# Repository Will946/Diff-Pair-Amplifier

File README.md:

# Differential Pair Amplifier for Force Sensing Applications

---

## Overview

A fully differential JFET-based amplifier designed to condition small analog signals from pressure transducers. The amplifier takes in a weak differential signal and amplifies it for readback by a microcontroller. The design is compact enough to mount close to the sensor, minimizing noise pickup before amplification.

Typical use cases for this amplifier topology include:
- Pressure and force transducer signal conditioning
- Strain gauge bridge amplification
- Low-level differential sensor readout in embedded systems
- Any application requiring rejection of common-mode noise on a differential signal line

---

## Circuit Architecture

The amplifier is a **common-source differential pair** using two JFE150DCKR N-channel JFETs with resistive drain loads, biased by a JFET current mirror tail current source.

- **Topology:** Common-source differential pair with resistive load
- **Devices:** 2x JFE150DCKR (signal pair) + 2x JFE150DCKR (current mirror)
- **Drain resistors:** Rp1 = Rn1 = 330 Ohm
- **Tail current:** 24 mA
- **Bias point:** V_GS = 188 mV, I_D = 12.1 mA per branch
- **Supply voltage:** V_DD = 8 V
- **Load capacitance:** 1 pF

---

## DC Operating Point

| Parameter | Value |
|---|---|
| Supply voltage (V_DD) | 8 V |
| Drain voltage (Voutp / Voutn) | 4.02 V |
| Drain current per branch | 12.1 mA |
| Tail current | 24.1 mA |
| Gate bias voltage | 188 mV |
| Total DC current | ~48 mA |
| Total DC power | ~0.38 W |

The drain voltage sits at 4.02 V - midway in the 0-8 V supply range - providing symmetric output swing headroom for both positive and negative signal excursions.

---

## Simulated AC Performance

| Parameter | Simulated |
|---|---|
| Midband gain (Avd) | 20.5 dB |
| -3 dB frequency | 5.05 MHz |
| Unity gain frequency (UGF) | 51.6 MHz |
| Output Vpp (transient) | 1.09 V |
| Total DC current | ~48 mA |
| Power consumption | ~0.38 W |

### Gain

Simulated midband differential gain is **20.5 dB**. In application this means the amplifier produces roughly 10x voltage amplification of the sensor signal before it reaches the microcontroller, giving the ADC a much larger and cleaner signal to digitize than the raw transducer output.

### Bandwidth

The -3 dB frequency is **5.05 MHz** and the UGF is **51.6 MHz**.

The -3 dB frequency is the point at which gain drops 3 dB from its midband value. Signals below this frequency are amplified at full gain; signals above it begin to attenuate. For a pressure transducer reading force on a robotic arm, relevant signal frequencies are well below 1 MHz, so the 5.05 MHz -3 dB comfortably covers the application bandwidth with margin to spare.

The UGF is the frequency at which gain falls to 0 dB - the amplifier is no longer amplifying above this point. At 51.6 MHz this sets the upper bound of useful operation and also indicates the stability behavior when used in a closed-loop system.

### Transient

A 100 mVpp input sine wave at 1 kHz produces a clean **1.09 V peak-to-peak** output with no visible clipping, confirming the amplifier operates linearly at this signal level and delivers sufficient swing to drive a microcontroller ADC input.

---

## PCB Layout

- **Board size:** 20 mm x 20 mm
- **Layer stackup:** 4 layers (Top - GND - Vdrain - GND)
- **Connector type:** SMA
- Input and power connections on the top layer
- Output connections on the bottom layer
- Left/right split layout - positive non-inverting side on the left, negative inverting side on the right, current mirror in the center
- Layout mirrors the schematic topology for easier debugging and trace routing

---

## Simulation Setup

All simulations were run in ngspice via KiCAD.

**DC Operating Point (.op)**
- Static analysis to verify node voltages and branch currents

**AC Analysis**
- Command: `.ac dec 100 100 5G`
- Input AC amplitude set to 1 V differential (Vgatep1 = +1, Vgaten1 = -1)
- Differential gain plotted as `V(/Voutp) - V(/Voutn)` in dB

**Transient Analysis**
- Command: `.tran 1u 10m`
- Input: 100 mVpp sine wave at 1 kHz

---

## Files

| File | Description |
|---|---|
| `Differential_Pair_Amplifier.kicad_sch` | Main schematic |
| `Differential_Pair_Amplifier.kicad_pcb` | PCB layout |
| `Bodeplot.png` | AC gain and phase vs frequency |
| `DC_Analysis.png` | DC operating point simulation |
| `Transient_Analsyis.png` | Transient input/output waveforms |
| `PCB.png` | 3D render of PCB |

---

## Known Limitations

- Bandwidth is limited by the resistive load topology - the dominant pole is set by R_D and the Miller capacitance of the JFE150
- A future revision with an active MOSFET load would significantly improve bandwidth while maintaining gain

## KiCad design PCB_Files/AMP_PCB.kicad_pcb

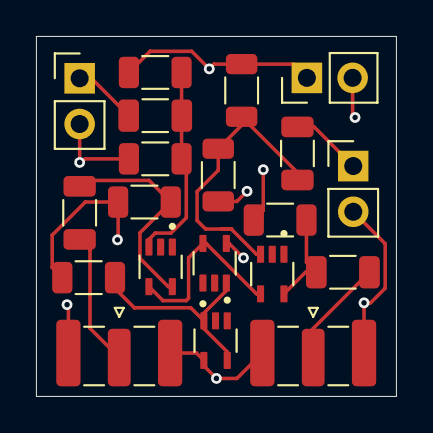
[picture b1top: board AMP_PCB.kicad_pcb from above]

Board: 4 copper layers, 20.0 x 20.0 mm, 20 parts (0 on the bottom side), 12 nets.

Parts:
CnG1: 100uF; C_1206_3216Metric
CnO1: 1nF; C_1206_3216Metric
CpG1: 100uF; C_1206_3216Metric
CpO1: 1nF; C_1206_3216Metric
Ibrchn1: JFE150DCKR; TRANS_JFE150DCKR
Ibrchp1: JFE150DCKR; TRANS_JFE150DCKR
Mirr1, Mirr2: JFE150DCKR; TRANS_JFE150DCKR
PHD1: Conn_01x02_Pin; PinHeader_1x02_P2.54mm_Vertical
PHGN1: Conn_01x02_Pin; PinHeader_1x02_P2.54mm_Vertical
PHGP1: Conn_01x02_Pin; PinHeader_1x02_P2.54mm_Vertical
Rm1: 316; R_1206_3216Metric
Rn1: 330; R_1206_3216Metric
RnG1: 1000; R_1206_3216Metric
RnG2: 24; R_1206_3216Metric
Rp1: 330; R_1206_3216Metric
RpG1: 1000; R_1206_3216Metric
RpG2: 24; R_1206_3216Metric
VnO1: Conn_Coaxial; SMA_Samtec_SMA-J-P-H-ST-EM1_EdgeMount
VpO1: Conn_Coaxial; SMA_Samtec_SMA-J-P-H-ST-EM1_EdgeMount

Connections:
/Vgaten1: CnG1.2, PHGN1.1
/Vgatep1: CpG1.1, PHGP1.1
/VoutTot: Ibrchn1.4 (S), Ibrchp1.4 (S), Mirr2.5 (D)
/Voutm1: Mirr1.3 (G), Mirr1.5 (D), Mirr2.3 (G), Rm1.2
/Voutn: CnO1.1, Ibrchn1.5 (D), Rn1.2
/Voutp: CpO1.1, Ibrchp1.5 (D), Rp1.2
GND: Mirr1.4 (S), Mirr2.4 (S), PHD1.2, PHGN1.2, PHGP1.2, RnG2.2, RpG2.2, VnO1.2 (Ext), VpO1.2 (Ext)
unnamed: CnG1.1, Ibrchn1.3 (G), RnG1.2, RnG2.1
unnamed: CpG1.2, Ibrchp1.3 (G), RpG1.2, RpG2.1
unnamed: CnO1.2, VnO1.1 (In)
unnamed: CpO1.2, VpO1.1 (In)
Vdrain: PHD1.1, Rm1.1, Rn1.1, RnG1.1, Rp1.1, RpG1.1
